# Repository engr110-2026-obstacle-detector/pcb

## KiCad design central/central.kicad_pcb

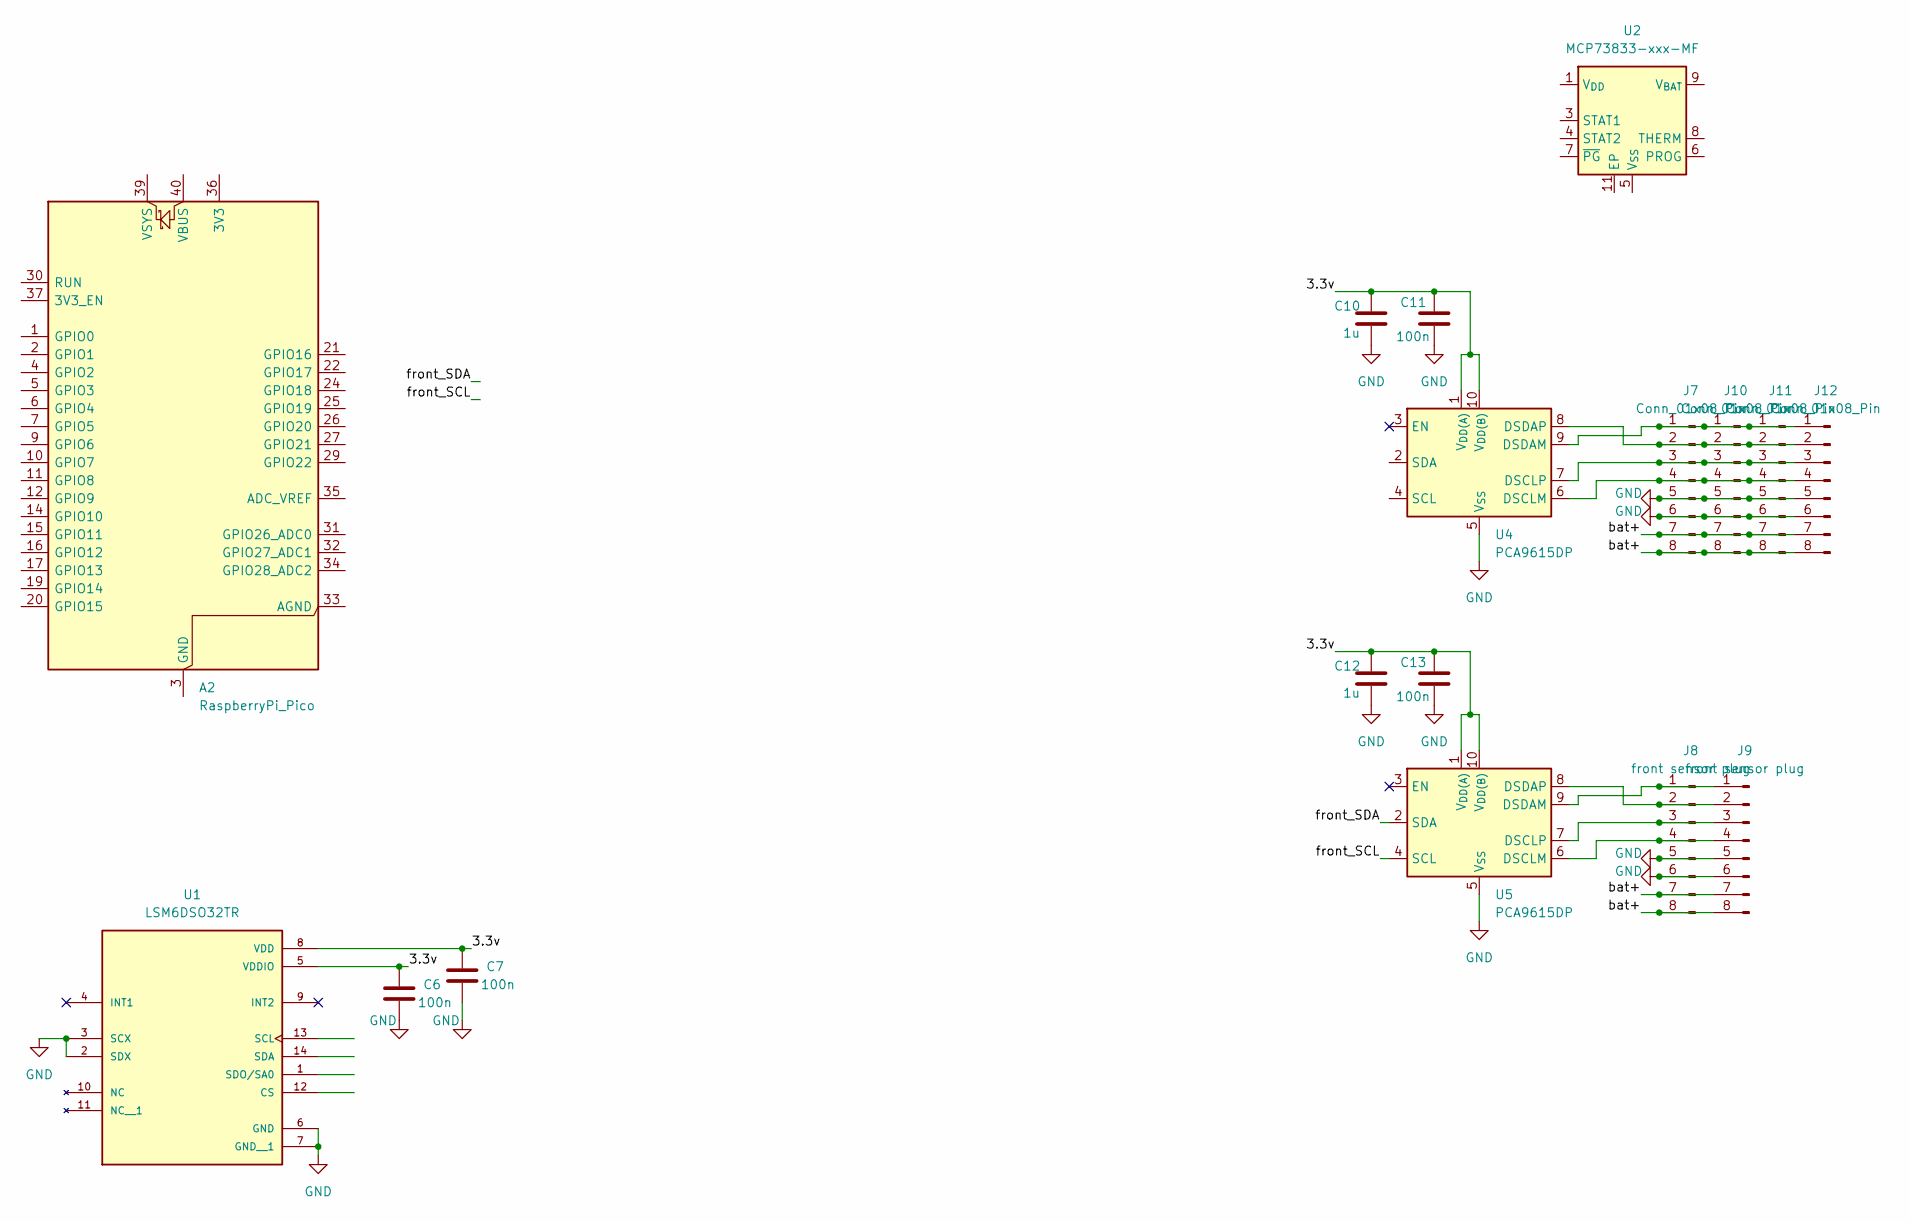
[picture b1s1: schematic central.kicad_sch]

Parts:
A2: RaspberryPi_Pico; RaspberryPi_Pico_Common_Unspecified
C6, C7, C11, C13: 100n; C_0603_1608Metric
C10, C12: 1u; C_0603_1608Metric
J7, J10, J11, J12: Conn_01x08_Pin; JST_XH_B8B-XH-AM_1x08_P2.50mm_Vertical
J8, J9: front sensor plug; JST_XH_B8B-XH-AM_1x08_P2.50mm_Vertical
U1: LSM6DSO32TR; XDCR_LSM6DSO32TR; PARTREV 1
U2: MCP73833-xxx-MF; DFN-10-1EP_3x3mm_P0.5mm_EP1.58x2.35mm
U4, U5: PCA9615DP; TSSOP-10_3x3mm_P0.5mm

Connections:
/3.3v: C6.1, C7.1, C10.1, C11.1, C12.1, C13.1, U1.5 (VDDIO), U1.8 (VDD), U4.1 (V_{DD(A)}), U4.10 (V_{DD(B)}), U5.1 (V_{DD(A)}), U5.10 (V_{DD(B)})
/bat+: J7.7, J7.8, J8.7, J8.8, J9.7, J9.8, J10.7, J10.8, J11.7, J11.8, J12.7, J12.8
/front_SCL: U5.4 (SCL)
/front_SDA: U5.2 (SDA)
GND: C6.2, C7.2, C10.2, C11.2, C12.2, C13.2, J7.5, J7.6, J8.5, J8.6, J9.5, J9.6, J10.5, J10.6, J11.5, J11.6, J12.5, J12.6, U1.2 (SDX), U1.3 (SCX), U1.6 (GND), U1.7 (GND__1), U4.5 (V_{SS}), U5.5 (V_{SS})
unnamed: A2.3 (GND), A2.8 (GND), A2.13 (GND), A2.18 (GND), A2.23 (GND), A2.28 (GND), A2.38 (GND)
unnamed: J8.1, J9.1, U5.9 (DSDAM)
unnamed: J8.2, J9.2, U5.8 (DSDAP)
unnamed: J8.3, J9.3, U5.7 (DSCLP)
unnamed: J8.4, J9.4, U5.6 (DSCLM)
unnamed: J7.1, J10.1, J11.1, J12.1, U4.9 (DSDAM)
unnamed: J7.2, J10.2, J11.2, J12.2, U4.8 (DSDAP)
unnamed: J7.3, J10.3, J11.3, J12.3, U4.7 (DSCLP)
unnamed: J7.4, J10.4, J11.4, J12.4, U4.6 (DSCLM)
unnamed: U2.1 (V_{DD}), U2.2 (V_{DD})
unnamed: U2.9 (V_{BAT}), U2.10 (V_{BAT})

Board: 2 copper layers, 16 parts (0 on the bottom side), 12 nets, no tracks yet.

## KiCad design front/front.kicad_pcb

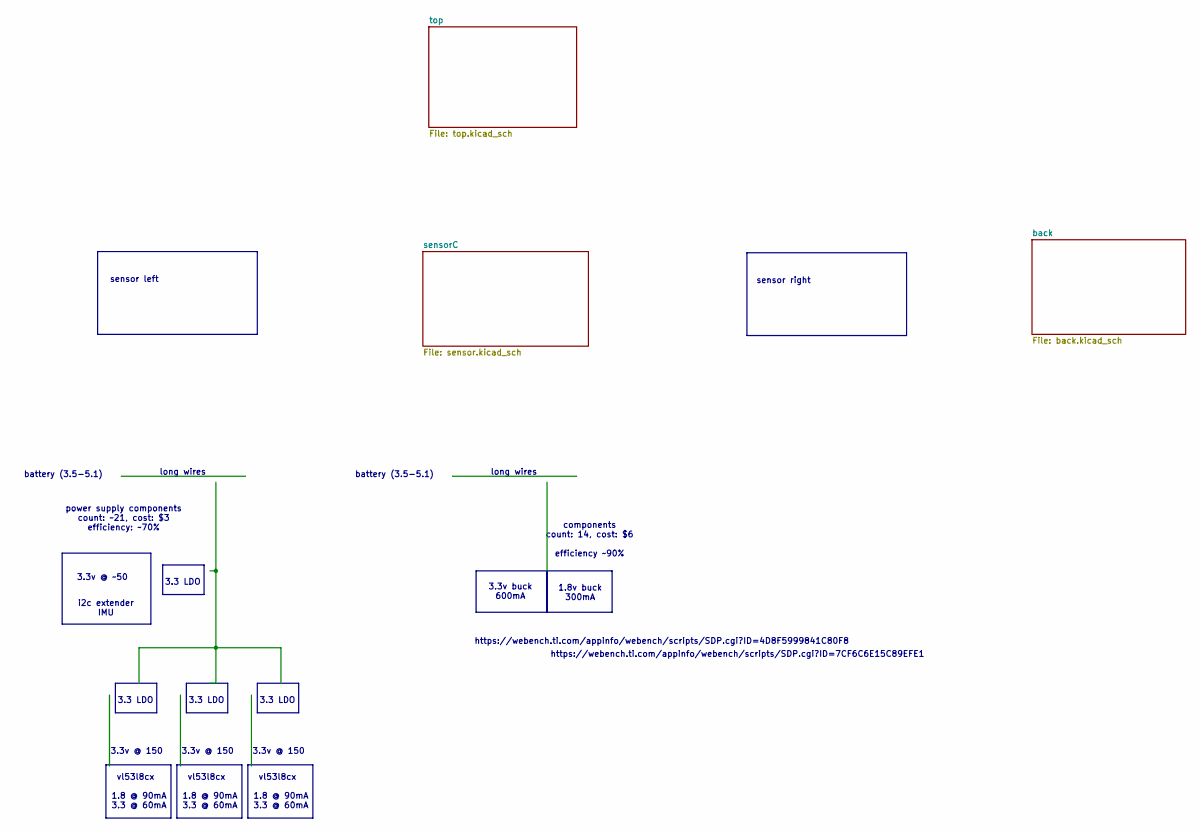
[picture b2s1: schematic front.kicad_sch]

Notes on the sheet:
1.8 @ 90mA 3.3 @ 60mA
power supply components count: ~21, cost: $3 efficiency: ~70%
vl53l8cx
3.3 LDO
sensor right
battery (3.5-5.1)
3.3v @ ~50
3.3v @ 150
https://webench.ti.com/appinfo/webench/scripts/SDP.cgi?ID=7CF6C6E15C89EFE1
3.3v buck 600mA
https://webench.ti.com/appinfo/webench/scripts/SDP.cgi?ID=4D8F5999841C80F8
long wires
sensor left
i2c extender IMU
components count: 14, cost: $6 efficiency ~90%
1.8v buck 300mA

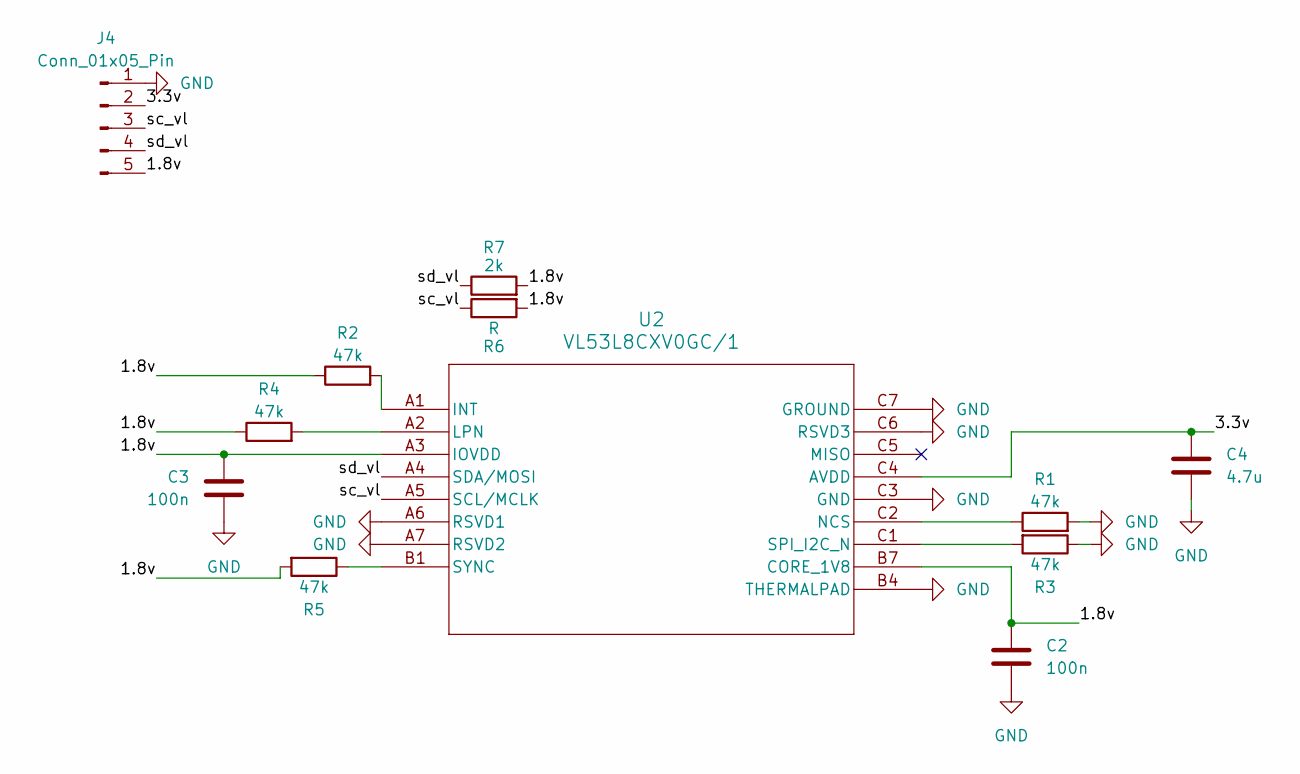
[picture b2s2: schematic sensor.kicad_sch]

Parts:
C2, C3: 100n; C_0603_1608Metric
C4: 4.7u; C_0603_1608Metric
J4: Conn_01x05_Pin; PinHeader_1x05_P2.54mm_Horizontal
R1, R2, R3, R4, R5: 47k; R_0603_1608Metric
R6: R; R_0603_1608Metric
R7: 2k; R_0603_1608Metric
U2: VL53L8CXV0GC/1; IC17_LGA16_STM

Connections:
/sensorC/1.8v: C2.1, C3.1, J4.5, R2.1, R4.1, R5.2, R6.2, R7.2, U2.A3 (IOVDD), U2.B7 (CORE_1V8)
/sensorC/3.3v: C4.1, J4.2, U2.C4 (AVDD)
/sensorC/sc_vl: J4.3, R6.1, U2.A5 (SCL/MCLK)
/sensorC/sd_vl: J4.4, R7.1, U2.A4 (SDA/MOSI)
GND: C2.2, C3.2, C4.2, J4.1, R1.2, R3.1, U2.A6 (RSVD1), U2.A7 (RSVD2), U2.B4 (THERMALPAD), U2.C3 (GND), U2.C6 (RSVD3), U2.C7 (GROUND); also elsewhere on the board
unnamed: R2.2, U2.A1 (INT)
unnamed: R4.2, U2.A2 (LPN)
unnamed: R1.1, U2.C2 (NCS)
unnamed: R3.2, U2.C1 (SPI_I2C_N)
unnamed: R5.1, U2.B1 (SYNC)

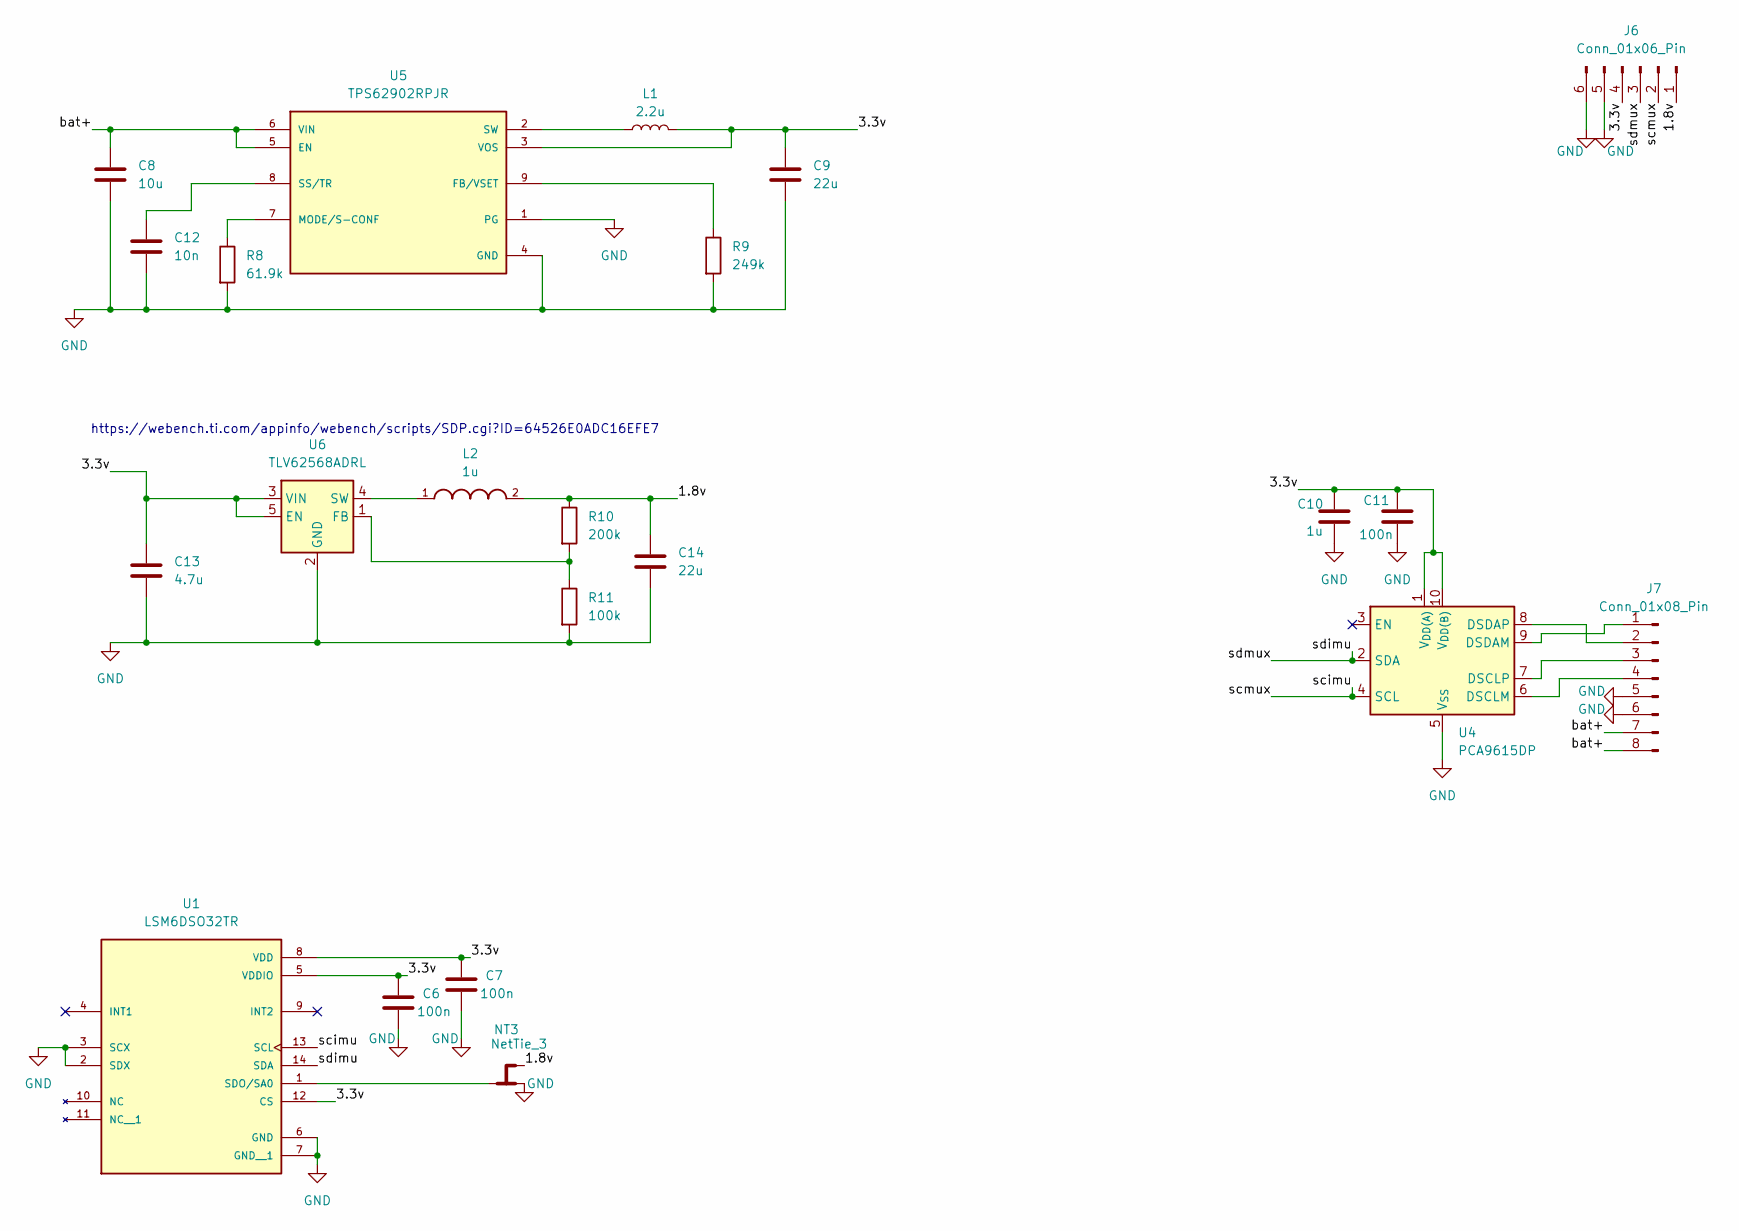
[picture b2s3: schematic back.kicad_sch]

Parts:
C6, C7, C11: 100n; C_0603_1608Metric
C8: 10u; C_0805_2012Metric; Mfr PN MSAST21GBB5106MTNA01
C9, C14: 22u; C_0805_2012Metric; Mfr PN GRM21BD70J226ME44L
C10: 1u; C_0603_1608Metric
C12: 10n; C_0603_1608Metric; Mfr PN GRM1857U1A103JA44D
C13: 4.7u; C_0603_1608Metric; Mfr PN C1608X7S1A475K080AC
J6: Conn_01x06_Pin; PinHeader_1x06_P2.54mm_Horizontal
J7: Conn_01x08_Pin; JST_XH_B8B-XH-AM_1x08_P2.50mm_Vertical
L1: 2.2u; WE-XHMI_4020; Mfr PN 74439323022
L2: 1u; INDC2520X120N; DigiKey_Part_Number 490-13053-1-ND
NT3: NetTie_3; SolderJumper-3_P1.3mm_Bridged12_RoundedPad1.0x1.5mm
R8: 61.9k; R_0603_1608Metric; Mfr PN CRCW060361K9FKEA
R9: 249k; R_0603_1608Metric; Mfr PN CRCW0603249KFKEA
R10: 200k; R_0603_1608Metric; Mfr PN CRCW0603200KFKEA
R11: 100k; R_0603_1608Metric; Mfr PN CRCW0603100KFKEA
U1: LSM6DSO32TR; XDCR_LSM6DSO32TR; PARTREV 1
U4: PCA9615DP; TSSOP-10_3x3mm_P0.5mm
U5: TPS62902RPJR; IC_TPS62902RPJR; PARTREV March 2021; DigiKey_Part_Number 296-TPS62902RPJRCT-ND
U6: TLV62568ADRL; SOT-563

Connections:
/back/1.8v: C14.1, J6.1, L2.2, NT3.3, R10.1
/back/3.3v: C6.1, C7.1, C9.1, C10.1, C11.1, C13.1, J6.4, L1.2, U1.5 (VDDIO), U1.8 (VDD), U1.12 (CS), U4.1 (V_{DD(A)}), U4.10 (V_{DD(B)}), U5.3 (VOS), U6.3 (VIN), U6.5 (EN)
/back/bat+: C8.1, J7.7, J7.8, U5.5 (EN), U5.6 (VIN)
/back/scimu: J6.2, U1.13 (SCL), U4.4 (SCL)
/back/sdimu: J6.3, U1.14 (SDA), U4.2 (SDA)
GND: C6.2, C7.2, C8.2, C9.2, C10.2, C11.2, C12.2, C13.2, C14.2, J6.5, J6.6, J7.5, J7.6, NT3.1, R8.2, R9.2, R11.2, U1.2 (SDX), U1.3 (SCX), U1.6 (GND), U1.7 (GND__1), U4.5 (V_{SS}), U5.1 (PG), U5.4 (GND), U6.2 (GND); also elsewhere on the board
unnamed: J7.1, U4.9 (DSDAM)
unnamed: J7.2, U4.8 (DSDAP)
unnamed: J7.3, U4.7 (DSCLP)
unnamed: J7.4, U4.6 (DSCLM)
unnamed: NT3.2, U1.1 (SDO/SA0)
unnamed: R9.1, U5.9 (FB/VSET)
unnamed: R8.1, U5.7 (MODE/S-CONF)
unnamed: C12.1, U5.8 (SS/TR)
unnamed: L1.1, U5.2 (SW)
unnamed: R10.2, R11.1, U6.1 (FB)
unnamed: L2.1, U6.4 (SW)

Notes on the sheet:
https://webench.ti.com/appinfo/webench/scripts/SDP.cgi?ID=64526E0ADC16EFE7

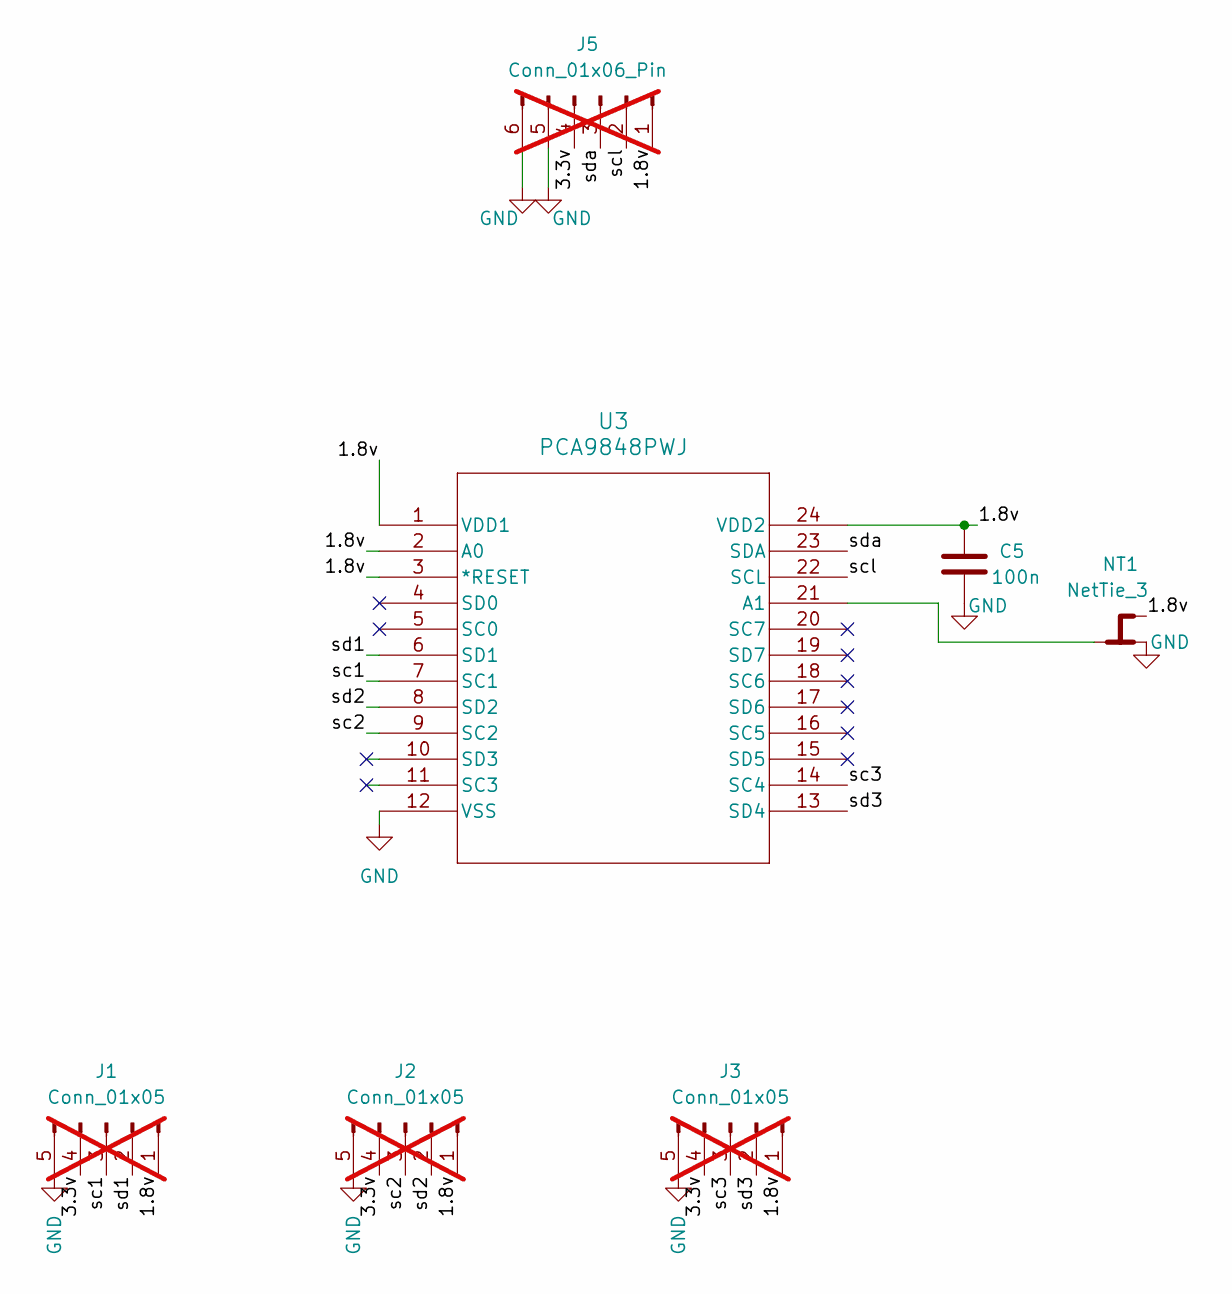
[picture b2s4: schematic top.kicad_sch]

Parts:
C5: 100n; C_0603_1608Metric
J1, J2, J3: Conn_01x05; PinHeader_1x05_P2.54mm_Vertical; not fitted
J5: Conn_01x06_Pin; PinSocket_1x06_P2.54mm_Vertical; not fitted
NT1: NetTie_3; SolderJumper-3_P1.3mm_Bridged12_RoundedPad1.0x1.5mm
U3: PCA9848PWJ; TSSOP24_SOT355-1_NEX_NXP

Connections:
/top/1.8v: C5.1, J1.1, J2.1, J3.1, J5.1, NT1.3, U3.1 (VDD1), U3.2 (A0), U3.3 (*RESET), U3.24 (VDD2)
/top/3.3v: J1.4, J2.4, J3.4, J5.4
/top/sc1: J1.3, U3.7 (SC1)
/top/sc2: J2.3, U3.9 (SC2)
/top/sc3: J3.3, U3.14 (SC4)
/top/scl: J5.2, U3.22 (SCL)
/top/sd1: J1.2, U3.6 (SD1)
/top/sd2: J2.2, U3.8 (SD2)
/top/sd3: J3.2, U3.13 (SD4)
/top/sda: J5.3, U3.23 (SDA)
GND: C5.2, J1.5, J2.5, J3.5, J5.5, J5.6, NT1.1, U3.12 (VSS); also elsewhere on the board
unnamed: NT1.2, U3.21 (A1)

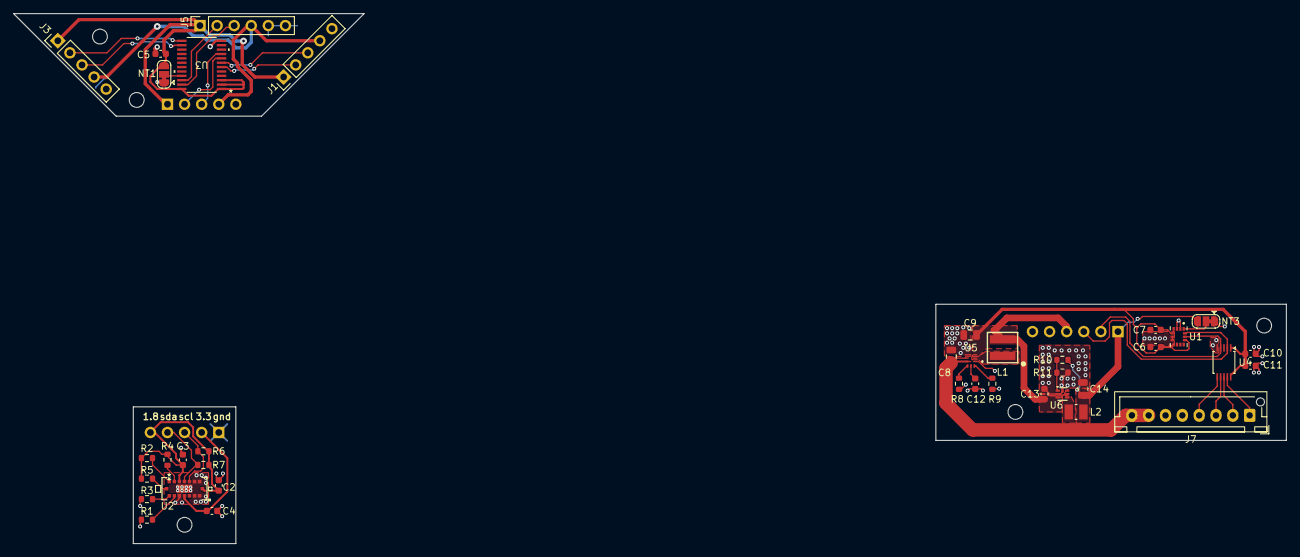
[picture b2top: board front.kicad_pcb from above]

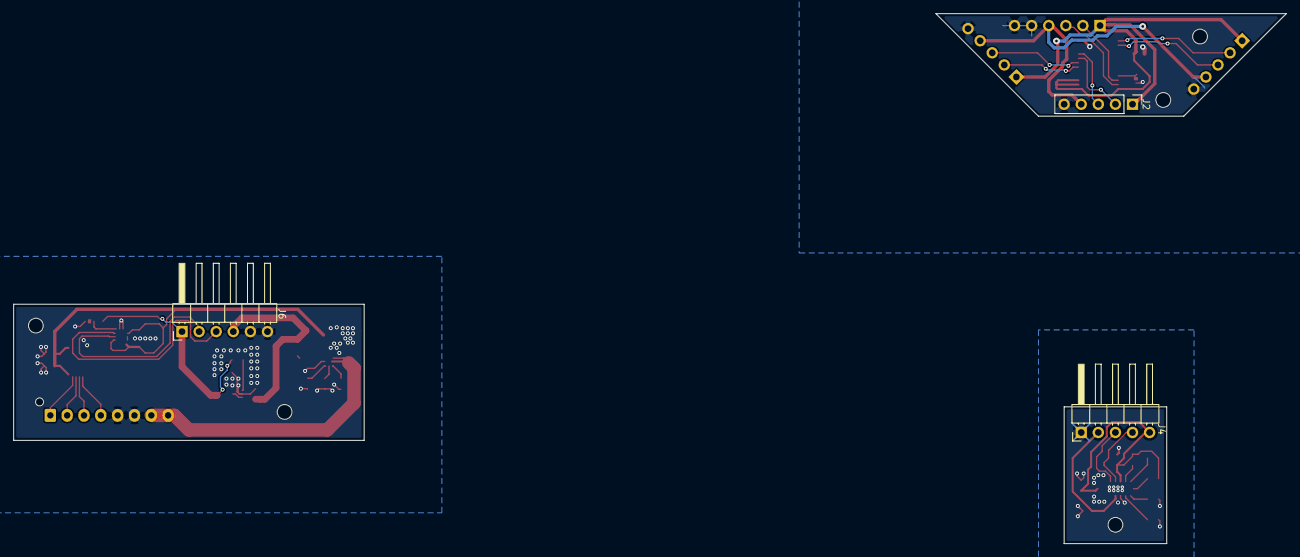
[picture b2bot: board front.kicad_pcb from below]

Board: 2 copper layers, 189.1 x 78.7 mm, 41 parts (3 on the bottom side), 37 nets.

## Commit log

2026-03-19 start adding components
2026-03-20 working
2026-03-21 script panelizes
2026-03-21 render images
2026-03-21 add step files
2026-03-21 add stls
2026-03-21 add some traces
2026-03-21 undo panelizing
2026-03-21 run script
2026-03-23 add more components
2026-03-30 begin layout
2026-04-03 layout front top
2026-04-03 history
2026-05-24 push changes
